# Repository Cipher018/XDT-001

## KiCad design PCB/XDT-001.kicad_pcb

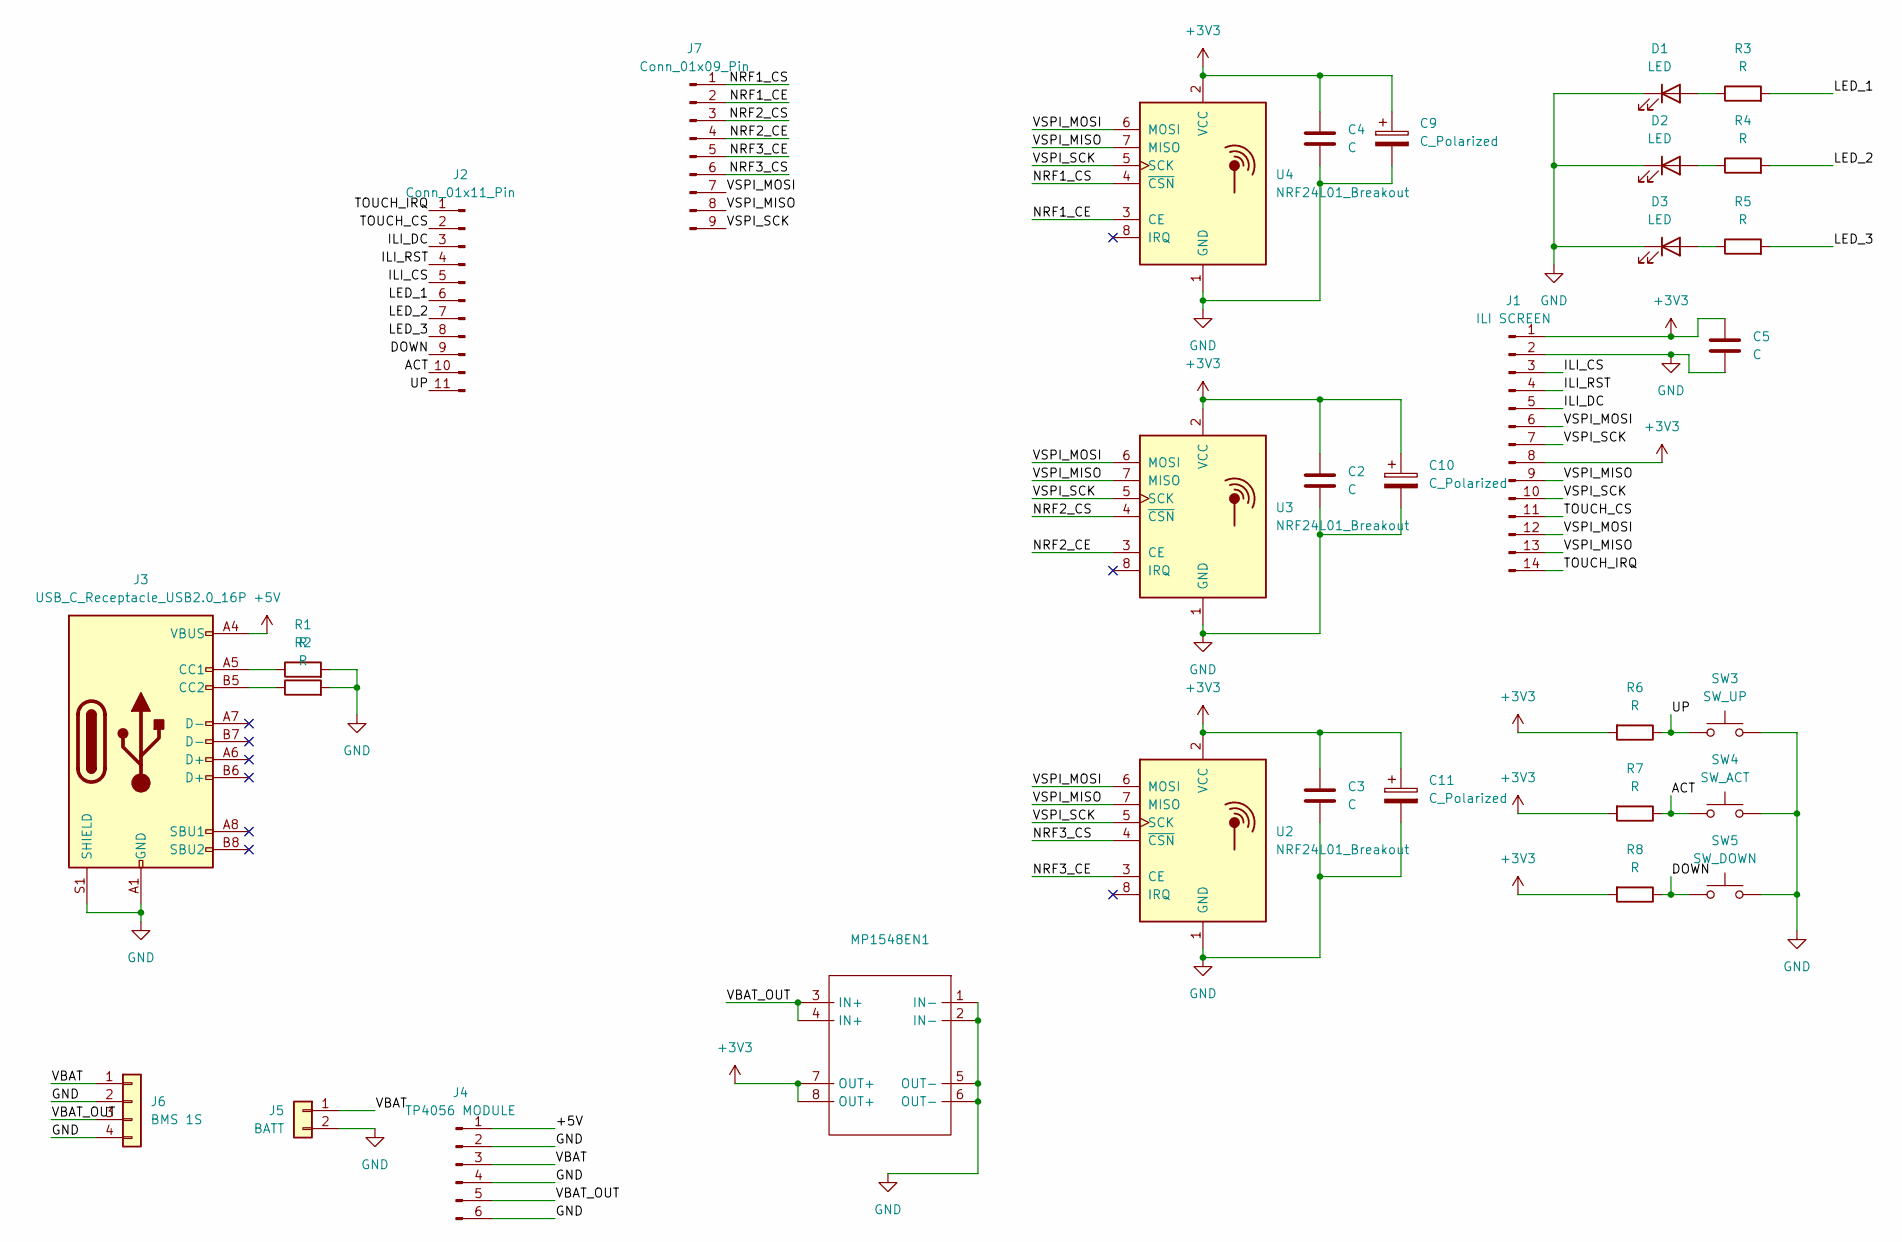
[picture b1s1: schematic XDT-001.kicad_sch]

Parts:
C2, C3, C4: C; C_0805_2012Metric_Pad1.18x1.45mm_HandSolder
C5: C; C_0805_2012Metric
C9, C10, C11: C_Polarized; CP_Radial_D5.0mm_P2.50mm
D1, D2, D3: LED; LED_D3.0mm
J1: ILI SCREEN; PinSocket_1x14_P2.54mm_Vertical
J2: Conn_01x11_Pin; PinSocket_1x11_P2.54mm_Horizontal
J3: USB_C_Receptacle_USB2.0_16P; USB_C_Receptacle_GCT_USB4105-xx-A_16P_TopMnt_Horizontal
J4: TP4056 MODULE; PinSocket_1x06_P2.54mm_Vertical
J5: BATT; PinSocket_1x02_P2.54mm_Vertical
J6: BMS 1S; PinSocket_1x04_P2.54mm_Vertical
J7: Conn_01x09_Pin; PinSocket_1x09_P2.54mm_Vertical
MP1548EN1: MP1548EN
R1, R2, R3, R4, R5, R6, R7, R8: R; R_0805_2012Metric_Pad1.20x1.40mm_HandSolder
SW3: SW_UP; SW_Cherry_MX_1.00u_PCB
SW4: SW_ACT; SW_Cherry_MX_1.00u_PCB
SW5: SW_DOWN; SW_Cherry_MX_1.00u_PCB
U2, U3, U4: NRF24L01_Breakout; nRF24L01_Breakout

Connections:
+3V3: C2.1, C3.1, C4.1, C5.1, C9.1, C10.1, C11.1, J1.1, J1.8, MP1548EN1.7 (OUT+), MP1548EN1.8 (OUT+), R6.2, R7.2, R8.2, U2.2 (VCC), U3.2 (VCC), U4.2 (VCC)
+5V: J3.A4 (VBUS), J3.A9 (VBUS), J3.B4 (VBUS), J3.B9 (VBUS), J4.1
/ACT: J2.10, R7.1, SW4.1
/DOWN: J2.9, R8.1, SW5.1
/ILI_CS: J1.3, J2.5
/ILI_DC: J1.5, J2.3
/ILI_RST: J1.4, J2.4
/LED_1: J2.6, R3.2
/LED_2: J2.7, R4.2
/LED_3: J2.8, R5.2
/NRF1_CE: J7.2, U4.3 (CE)
/NRF1_CS: J7.1, U4.4 (~CSN)
/NRF2_CE: J7.4, U3.3 (CE)
/NRF2_CS: J7.3, U3.4 (~CSN)
/NRF3_CE: J7.5, U2.3 (CE)
/NRF3_CS: J7.6, U2.4 (~CSN)
/TOUCH_CS: J1.11, J2.2
/TOUCH_IRQ: J1.14, J2.1
/UP: J2.11, R6.1, SW3.1
/VBAT: J4.3, J5.1, J6.1
/VBAT_OUT: J4.5, J6.3, MP1548EN1.3 (IN+), MP1548EN1.4 (IN+)
/VSPI_MISO: J1.9, J1.13, J7.8, U2.7 (MISO), U3.7 (MISO), U4.7 (MISO)
/VSPI_MOSI: J1.6, J1.12, J7.7, U2.6 (MOSI), U3.6 (MOSI), U4.6 (MOSI)
/VSPI_SCK: J1.7, J1.10, J7.9, U2.5 (SCK), U3.5 (SCK), U4.5 (SCK)
GND: C2.2, C3.2, C4.2, C5.2, C9.2, C10.2, C11.2, D1.1 (K), D2.1 (K), D3.1 (K), J1.2, J3.A1 (GND), J3.A12 (GND), J3.B1 (GND), J3.B12 (GND), J3.S1 (SHIELD), J4.2, J4.4, J4.6, J5.2, J6.2, J6.4, MP1548EN1.1 (IN-), MP1548EN1.2 (IN-), MP1548EN1.5 (OUT-), MP1548EN1.6 (OUT-), R1.2, R2.2, SW3.2, SW4.2, SW5.2, U2.1 (GND), U3.1 (GND), U4.1 (GND)
unnamed: D1.2 (A), R3.1
unnamed: D2.2 (A), R4.1
unnamed: D3.2 (A), R5.1
unnamed: J3.A5 (CC1), R1.1
unnamed: J3.B5 (CC2), R2.1

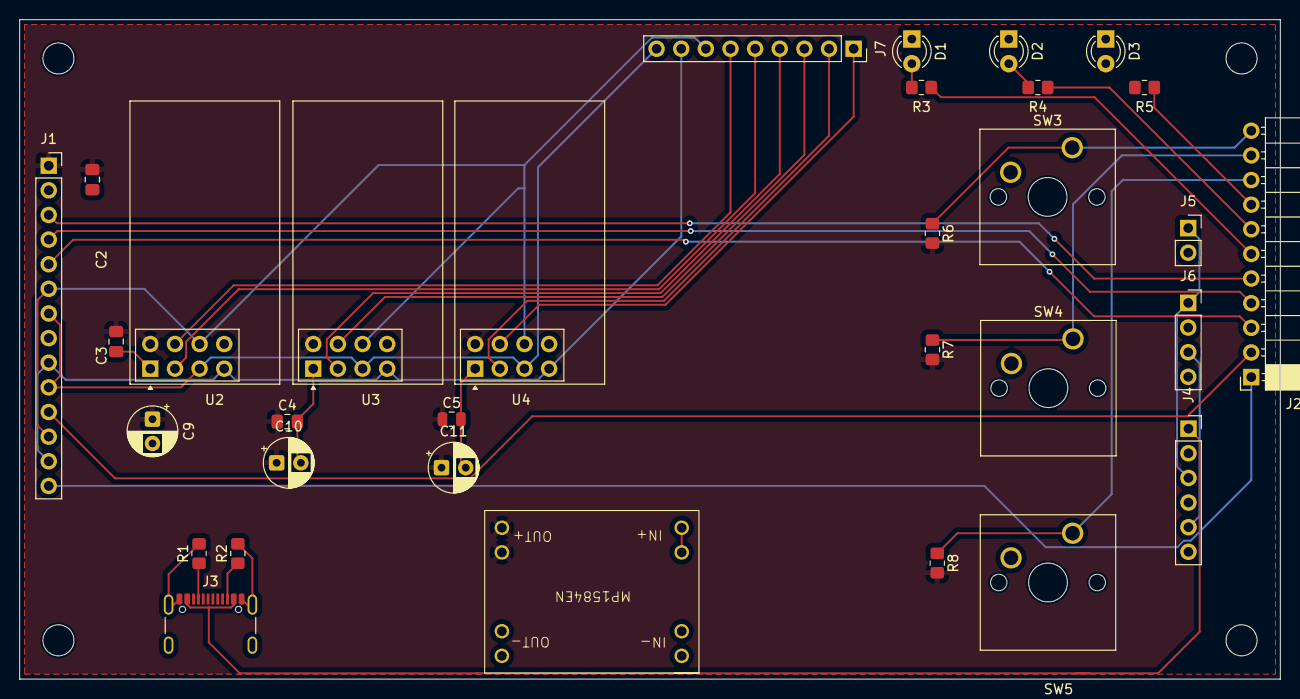
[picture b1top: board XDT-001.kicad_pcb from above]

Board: 2 copper layers, 130.0 x 68.0 mm, 32 parts (0 on the bottom side), 30 nets.

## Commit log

2026-04-05 Added root files
2026-04-05 Firts version of the firmware, only a few variables
2026-04-12 Import CAD files, BOM and PCB Files. Updated the firmware and added reference code from my legacy project
